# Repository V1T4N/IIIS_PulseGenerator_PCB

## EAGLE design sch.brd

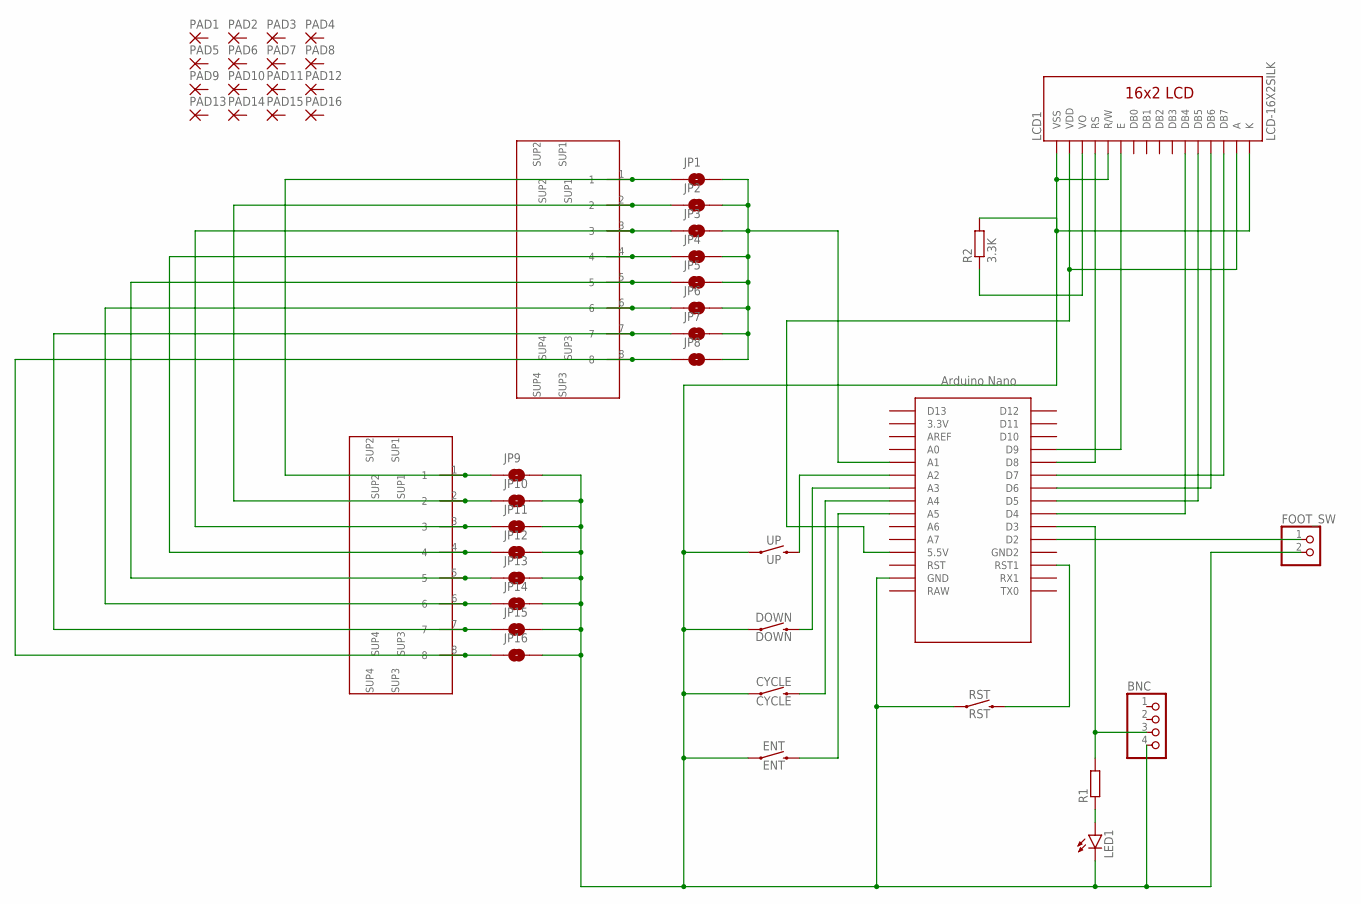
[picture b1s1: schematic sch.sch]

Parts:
BNC: PINHD-1X4; 1X04
CYCLE: CYCLE; TACTILE_SWITCH_PTH_6.0MM
DOWN: DOWN; TACTILE_SWITCH_PTH_6.0MM
ENT: ENT; TACTILE_SWITCH_PTH_6.0MM
FOOT_SW: PINHD-1X2; 1X02
JP1, JP2, JP3, JP4, JP5, JP6, JP7, JP8, JP9, JP10, JP11, JP12, JP13, JP14, JP15, JP16: JUMPER-SMT_2_NO_SILK; SMT-JUMPER_2_NO_SILK
LAN1, LAN2: RJ45
LCD1: LCD-16X2SILK; LCD-16X2
LED1: LED5MM
PAD1, PAD2, PAD3, PAD4, PAD5, PAD6, PAD7, PAD8, PAD9, PAD10, PAD11, PAD12, PAD13, PAD14, PAD15, PAD16: 1,6/0,8
R1: R-EU_0207/7; 0207/7
R2: 3.3K; 0207/7
RST: RST; TACTILE_SWITCH_PTH_6.0MM
U$1: NANO
UP: UP; TACTILE_SWITCH_PTH_6.0MM

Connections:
unnamed: LCD1.4 (RS), U$1.D8
unnamed: LCD1.6 (E), U$1.D9
unnamed: LCD1.11 (DB4), U$1.D4
unnamed: LCD1.12 (DB5), U$1.D5
unnamed: LCD1.13 (DB6), U$1.D6
unnamed: LCD1.14 (DB7), U$1.D7
unnamed: BNC.3, R1.2, U$1.D3
unnamed: LED1.A, R1.1
unnamed: U$1.A2, UP.3 (2)
unnamed: JP1.2, JP2.2, JP3.2, JP4.2, JP5.2, JP6.2, JP7.2, JP8.2, U$1.A1
unnamed: FOOT_SW.1, U$1.D2
unnamed: LCD1.2 (VDD), LCD1.15 (A), U$1.5V (5.5V)
unnamed: DOWN.3 (2), U$1.A3
unnamed: CYCLE.3 (2), U$1.A4
unnamed: ENT.3 (2), U$1.A5
unnamed: BNC.4, CYCLE.1, DOWN.1, ENT.1, FOOT_SW.2, JP9.2, JP10.2, JP11.2, JP12.2, JP13.2, JP14.2, JP15.2, JP16.2, LCD1.1 (VSS), LCD1.5 (R/W), LCD1.16 (K), LED1.K (C), R2.2, RST.1, U$1.GND, UP.1
unnamed: RST.3 (2), U$1.RST1
unnamed: JP2.1, JP10.1, LAN1.2, LAN2.2
unnamed: JP3.1, JP11.1, LAN1.3, LAN2.3
unnamed: JP4.1, JP12.1, LAN1.4, LAN2.4
unnamed: JP5.1, JP13.1, LAN1.5, LAN2.5
unnamed: JP6.1, JP14.1, LAN1.6, LAN2.6
unnamed: JP7.1, JP15.1, LAN1.7, LAN2.7
unnamed: JP8.1, JP16.1, LAN1.8, LAN2.8
unnamed: JP1.1, JP9.1, LAN1.1, LAN2.1
unnamed: LCD1.3 (VO), R2.1

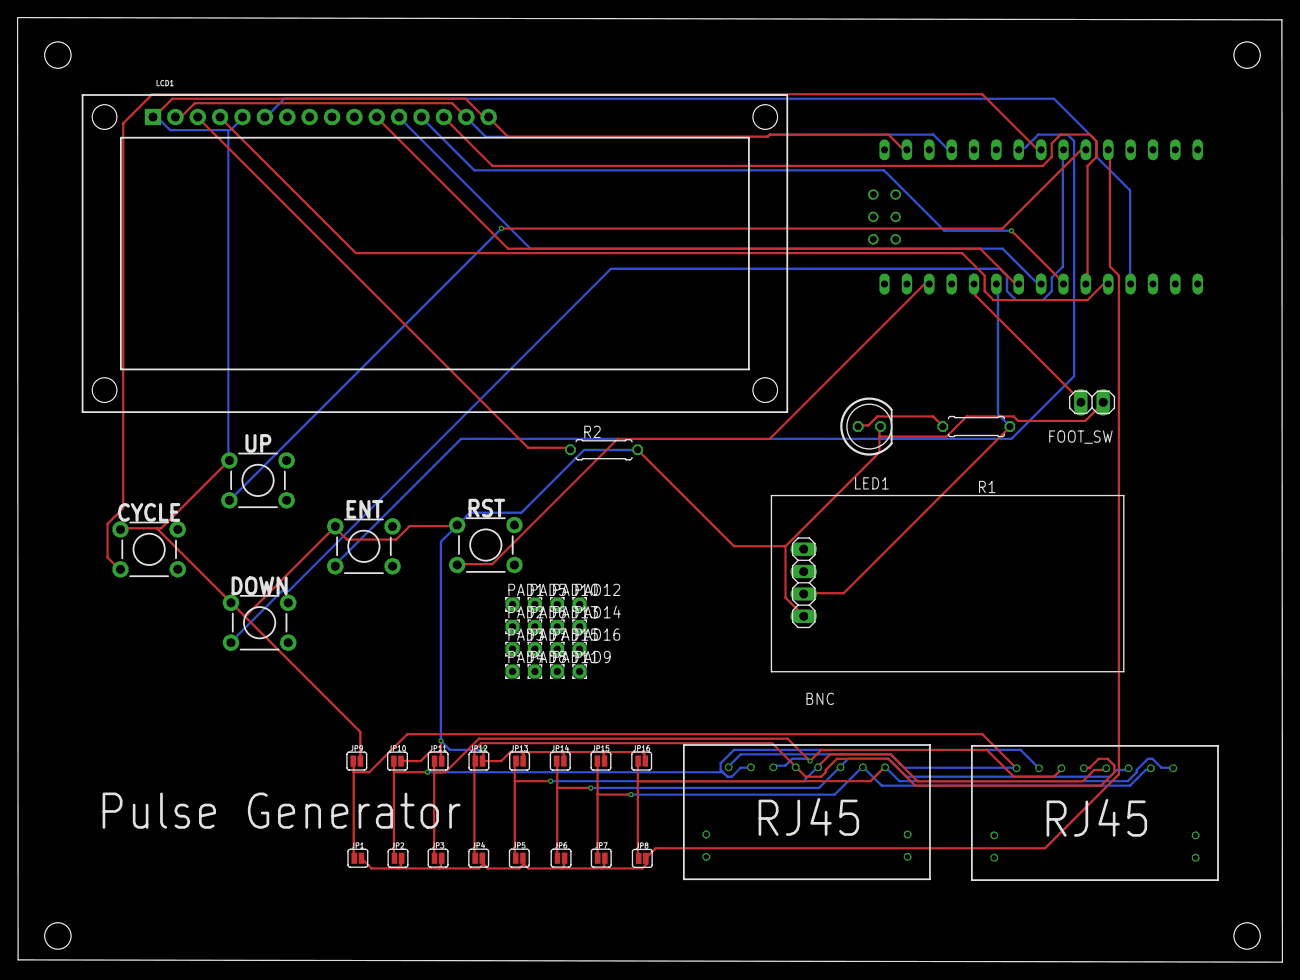
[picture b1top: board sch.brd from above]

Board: 2 copper layers, 143.6 x 107.2 mm, 46 parts (0 on the bottom side), 26 nets.

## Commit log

2019-05-16 add rj45

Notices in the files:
parts and their libraries:
SparkFun-Displays: Licensing: Creative Commons ShareAlike 4.0 International - https://creativecommons.org/licenses/by-sa/4.0
